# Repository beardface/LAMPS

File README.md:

LAMPS - The Open Hardware SLA Printer
-------------------------------------
LAMPS (Laser Arduino Mega Pololu Shield|SLA Printer) is an open control board and SLA printer design.  The SLA Printer strives to be a low-cost, small footprint (It is only 200mmx350mm!), highly capable SLA Printer. The build platform size is currently 100mmx100mm, but could probably be increased by someone who is motivated to enhance the design.

#License
The schematic for the OpenSL electronics are licensed under the GPL.

The printer and its associated parts are licensed under the Creative Commons Attribution-NonCommercial-ShareAlike 3.0 Unported License.

Basically, use my design all you want! :) But, don't sell it.  If you want an exception, contact me.

#LAMPS Board
LAMPS is the PCB control board that rides on top of an Arduino Mega 2560.  It provides Galvanometer control (Through 12 bit DACs).  It also controls the laser, buttons, Z Stepper Motor (Through Pololu Carrier), End Stops, LEDs, etc...  (It is the Brainz).

Version 1.0 of the LAMPS board has been manufactured and tested... I found a few issues with the board and am currently redesigning and removing a few unnecessary components for 1.1. Release date T.B.D.

#Firmware
The firmware for LAMPS is a fork of Marlin (The best open source RepRap firmware I know of), and can be found here: https://github.com/beardface/Marlin-OpenSL
The firmware is very much an active work-in-progress, and I encourage you to fork, and contribute.

#LAMPS Printer Parts -WARNING... THIS IS NOT UP TO DATE-
All of the parts are available as sketchup (skp) and stl files.

##Printed Parts
* 1x [Laser Mount](https://github.com/beardface/LAMPS/blob/master/parts/lasermount.stl)
* 1x [Mirror Mount](https://github.com/beardface/LAMPS/blob/master/parts/mirrormount.stl)
* 4x [Vibrating Vat Mount](https://github.com/beardface/LAMPS/blob/master/parts/vibrating_vat_mount.stl)
* 1x [Z-Axis Top Mount](https://github.com/beardface/LAMPS/blob/master/parts/z_top_mount.stl)
* 1x [Z-Axis Bottom Mount](https://github.com/beardface/LAMPS/blob/master/parts/z_bottom_mount.stl)
* 1x [Build Platform Mount](https://github.com/beardface/LAMPS/blob/master/parts/platform_mount.stl)
* 1x [Build Stage](https://github.com/beardface/LAMPS/blob/master/parts/build_platform_connector.stl)
* 1x Endstop Mount

##Laser Cut Parts
###Platform
Use 3/16"-1/4" thick acrylic for the platforms.
* 1x [Vat Platform](https://github.com/beardface/LAMPS/blob/master/parts/top_platform.svg)
* 1x [Component Platform](https://github.com/beardface/LAMPS/blob/master/parts/bottom_platform.svg)
* 1x 80mmx80mm 1/4"Acryilc Stage Mount (leftover part from cutting of top_platform)

###VAT
Use 1/4" Clear (Transparent) Acrylic for the VAT!
* 1x [Vat Back](https://github.com/beardface/LAMPS/blob/master/parts/vat_design/vat_back.svg)
* 1x [Vat Front](https://github.com/beardface/LAMPS/blob/master/parts/vat_design/vat_front.svg)
* 1x [Vat Bottom](https://github.com/beardface/LAMPS/blob/master/parts/vat_design/vat_bottom.svg)
* 1x [Vat Handle](https://github.com/beardface/LAMPS/blob/master/parts/vat_design/vat_handle.svg)
* 2x [Vat Sides](https://github.com/beardface/LAMPS/blob/master/parts/vat_design/vat_side.svg)

##Non-Printed Parts
* 1x NEMA 17 Stepper Motor (Low Profile!)
* 2x 8mm Smooth Rod (~260mm)
* 1x 8mm Threaded Rod (~260mm) and 2-M8 nuts
* 4x LM8UU Bearings
* 1x LAMPS Electronics Kit (w/Pololu and 2x endstops)
* 1x LAMPS PCB Build Platform
* 1x LAMPS Musimi 2020 Rail Kit and connectors
  * 4x  350mm 2020 Extrusions w/end tapping holes
  * 11x 160mm 2020 Extrusions
  * 1x  110mm 2020 Extrusion
* 1x LAMPS Enclsoure & Hatch Kit
* 1x 405nm Laser (20mw-150mw) -- Build properties/cure time/etc... vary by laser!
* 1x 3" Square Mirror
* 1x Laser Galvo Set (20kpps) w/power supply
 * Resistance Configuration (Note to Self)
  * AXIS  |  SIZE     | GAIN      | LF         | HF        | LINEAR
  * X     |  4.96Kohm | 4.68 Kohm | 26.36 Kohm | 4.78 Kohm | 1.75 Kohm
  * Y     |  6.1Kohm  | 4.18 Kohm | 26.47 Kohm | 4.37 Kohm | 2.3 Kohm
* 1x +/-12V Power Supply (~1-3Amps)
* USB Cable
* Power Cable
* Screws, Nuts, Wires, Solder, Patience

##Optional (But Useful) Non-Printed Parts
* 1xLCD Screen
* 1xSD Card Reader (and corresponding circuit... T.B.D.)
* 1x Power Switch (110-250VAC), lighted
* 1x Power Terminal (Two combine power into single input)
* 1x 3-Prong Power Jack
 
###LAMPS IS A WORK IN PROGRESS.

##Some words of Caution
* Careful with 110-250VAC, it can --bite-- Seriously Harm you if you aren't careful
* Some 405nm Resins can be toxic while curing- take the appropriate measures to ensure you are working in a well ventelated room

~LAMPS design, details, and parts list are provided without any warranty or gaurantee- this is a community project, so lets work together to solve issues that may arise!

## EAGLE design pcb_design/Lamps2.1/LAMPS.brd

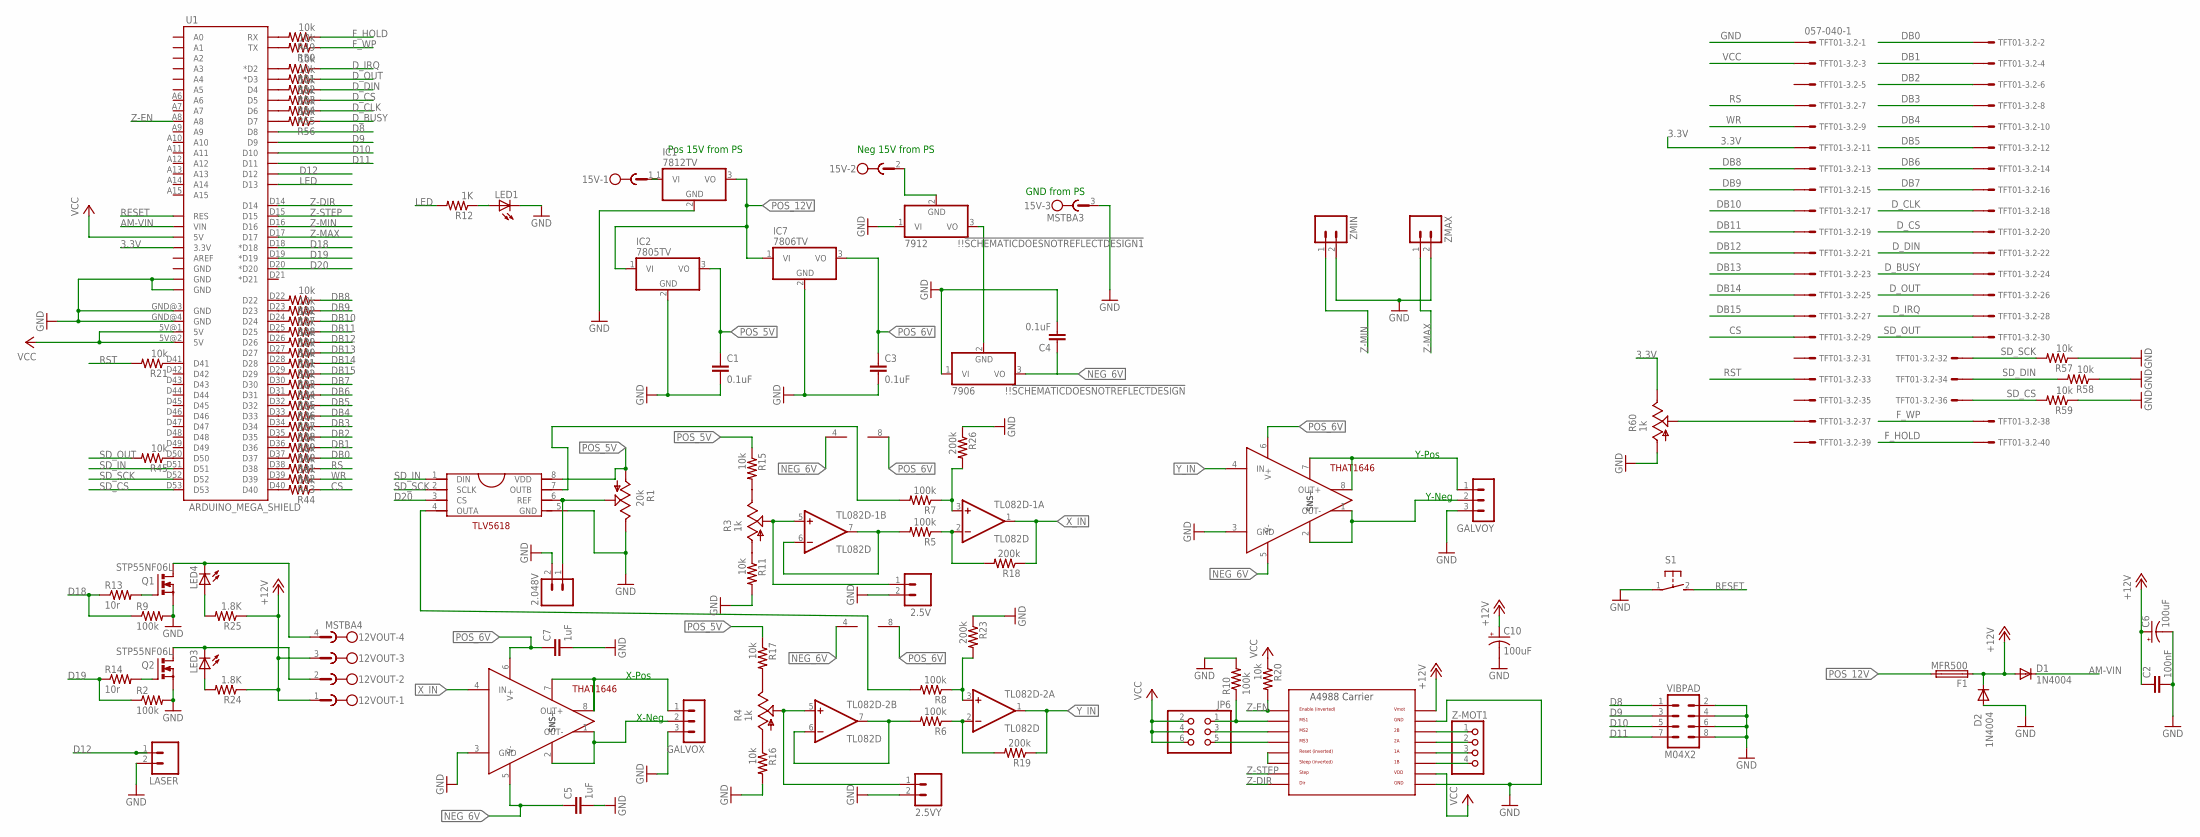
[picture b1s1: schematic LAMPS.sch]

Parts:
2.5V, 2.5VY, 2.048V: M02PTH; 1X02
12VOUT: MSTBA4
15V: MSTBA3; MPN 1757255
!!!SCHEMATICDOESNOTREFLECTDESIGN: 7906; TO220V; MPN KA7906TU
!!!SCHEMATICDOESNOTREFLECTDESIGN1: 7912; TO220V; MPN KA7906TU
C1, C3, C4: 0.1uF; C2.5-2
C2: 100nF; C0805
C5, C7: 1uF; C2.5-2
C6, C10: 100uF; 153CLV-0605
D1, D2: 1N4004; DO41-10
F1: MFR500
GALVOX: 3PIN-HEADER
GALVOY: 3PIN-HEADER
IC1: 7812TV; TO220V
IC2: 7805TV; TO220V
IC7: 7806TV; TO220V
JP6: PINHD-2X3; 2X03
LASER: M02PTH; 1X02
LED1, LED3, LED4: LEDCHIP-LED0805; CHIP-LED0805
Q1, Q2: STP55NF06L; TO220BV; MPN IRF1010EZPBF
R1: 20k; B25P
R2, R5, R6, R7, R8, R9, R10: 100k; R0805
R3, R4, R60: 1k; B25P
R11, R15, R16, R17, R20, R21, R22, R27, R28, R29, R30, R31, R32, R33, R34, R35, R36, R37, R38, R39, R40, R41, R42, R43, R44, R45, R49, R50, R51, R52, R53, R54, R55, R56, R57, R58, R59: 10k; R0805
R12: 1K; R0805
R13: 10r; R0805
R14: 10r; M0805
R18, R19, R23, R26: 200k; R0805
R24, R25: 1.8K; R0805
S1: 31-XX; B3F-31XX
TFT01-3.2: 057-040-1
TL082D-1, TL082D-2: TL082D; SO08
U1: ARDUINO_MEGA_SHIELD
U$1, U$4: THAT1646; MPN THAT1646P08-U
U$2: THAT1646SMD; TLV5618
U$8: A4988BREAKOUT
VIBPAD: M04X2; 2X4
Z-MOT1: PINHD-1X4; 1X04
ZMAX: M02PTH; 1X02
ZMIN: M02PTH; 1X02

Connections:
3.3V: R60.E, TFT01-3.2.11, U1.3.3V
+12V: 12VOUT.1, 12VOUT.3, C2.1, C6.+, C10.+, D1.A, D2.C, F1.1, R24.1, R25.1, U$8.VMOT
AM-VIN: D1.C, U1.VIN
CS: R44.1, TFT01-3.2.29
D8: U1.D8, VIBPAD.1
D9: U1.D9, VIBPAD.3
D10: U1.D10, VIBPAD.5
D11: U1.D11, VIBPAD.7
D12: LASER.1, U1.D12
D18: R9.1, R13.1, U1.D18 (*D18)
D19: R2.1, R14.1, U1.D19 (*D19)
D20: U1.D20 (*D20), U$2.3 (CS)
DB0: R41.1, TFT01-3.2.2
DB1: R40.1, TFT01-3.2.4
DB2: R39.1, TFT01-3.2.6
DB3: R38.1, TFT01-3.2.8
DB4: R37.1, TFT01-3.2.10
DB5: R36.1, TFT01-3.2.12
DB6: R35.1, TFT01-3.2.14
DB7: R34.1, TFT01-3.2.16
DB8: R22.1, TFT01-3.2.13
DB9: R27.1, TFT01-3.2.15
DB10: R28.1, TFT01-3.2.17
DB11: R29.1, TFT01-3.2.19
DB12: R30.1, TFT01-3.2.21
DB13: R31.1, TFT01-3.2.23
DB14: R32.1, TFT01-3.2.25
DB15: R33.1, TFT01-3.2.27
D_BUSY: R56.1, TFT01-3.2.24
D_CLK: R55.1, TFT01-3.2.18
D_CS: R54.1, TFT01-3.2.20
D_DIN: R53.1, TFT01-3.2.22
D_IRQ: R51.1, TFT01-3.2.28
D_OUT: R52.1, TFT01-3.2.26
F_HOLD: R49.1, TFT01-3.2.40
F_WP: R50.1, TFT01-3.2.38
GND: 2.5V.2, 2.5VY.2, 2.048V.2, 15V.3, !!!SCHEMATICDOESNOTREFLECTDESIGN.1 (VI), !!!SCHEMATICDOESNOTREFLECTDESIGN1.1 (VI), C1.2, C2.2, C3.2, C4.2, C5.2, C6.-, C7.2, C10.-, GALVOX.3, GALVOY.3, IC1.2 (GND), IC2.2 (GND), IC7.2 (GND), LASER.2, LED1.C, Q1.S, Q2.S, R1.E, R2.2, R9.2, R10.2, R11.2, R16.2, R23.1, R26.1, R57.1, R58.1, R59.1, R60.A, S1.1, TFT01-3.2.1, U1.GND@0 (GND), U1.GND@1 (GND), U1.GND@3 (GND), U1.GND@4 (GND), U$1.3 (GND), U$2.5 (GND), U$4.3 (GND), U$8.GND, U$8.GND@0 (GND), VIBPAD.2, VIBPAD.4, VIBPAD.6, VIBPAD.8, ZMAX.2, ZMIN.2
GND_0: D2.A
LED: R12.2, U1.D13
unnamed: 12VOUT.2, LED3.C, Q2.D
unnamed: R21.1, U1.D41
unnamed: !!!SCHEMATICDOESNOTREFLECTDESIGN.2 (GND), !!!SCHEMATICDOESNOTREFLECTDESIGN1.3 (VO)
unnamed: R4.A, R16.1
unnamed: R4.E, R17.2
unnamed: 2.048V.1, R1.S, U$2.6 (REF)
unnamed: 12VOUT.4, LED4.C, Q1.D
unnamed: R3.A, R11.1
unnamed: R3.E, R15.2
unnamed: 2.5VY.1, R4.S, TL082D-2.5 (+IN)
unnamed: 2.5V.1, R3.S, TL082D-1.5 (+IN)
unnamed: GALVOX.2, U$1.1 (OUT-), U$1.2 (SNS-)
unnamed: GALVOX.1, U$1.7 (SNS+), U$1.8 (OUT+)
unnamed: R5.2, TL082D-1.6 (-IN), TL082D-1.7 (OUT)
unnamed: R5.1, R18.2, TL082D-1.2 (-IN)
unnamed: R7.2, U$2.7 (OUTB)
unnamed: R7.1, R26.2, TL082D-1.3 (+IN)
unnamed: R6.2, TL082D-2.6 (-IN), TL082D-2.7 (OUT)
unnamed: R22.2, U1.D22
unnamed: R6.1, R19.2, TL082D-2.2 (-IN)
unnamed: R8.2, U$2.4 (OUTA)
unnamed: R8.1, R23.2, TL082D-2.3 (+IN)
unnamed: R27.2, U1.D23
unnamed: GALVOY.2, U$4.1 (OUT-), U$4.2 (SNS-)
unnamed: GALVOY.1, U$4.7 (SNS+), U$4.8 (OUT+)
unnamed: R28.2, U1.D24
unnamed: R29.2, U1.D25
unnamed: R30.2, U1.D26
unnamed: R31.2, U1.D27
unnamed: R32.2, U1.D28
unnamed: R33.2, U1.D29
unnamed: R34.2, U1.D30
unnamed: R35.2, U1.D31
unnamed: R36.2, U1.D32
unnamed: R37.2, U1.D33
unnamed: R38.2, U1.D34
unnamed: JP6.3, U$8.MS2
unnamed: U$8.RST, U$8.SLP (SLEEP)
unnamed: JP6.5, U$8.MS3
unnamed: JP6.1, R10.1, U$8.MS1
unnamed: U$8.2B, Z-MOT1.1
unnamed: U$8.2A, Z-MOT1.2
unnamed: U$8.1A, Z-MOT1.3
unnamed: U$8.1B, Z-MOT1.4
unnamed: LED3.A, R24.2
unnamed: LED1.A, R12.1
unnamed: Q2.G, R14.2
unnamed: Q1.G, R13.2
unnamed: R39.2, U1.D35
unnamed: LED4.A, R25.2
unnamed: R40.2, U1.D36
unnamed: R41.2, U1.D37
unnamed: R42.2, U1.D38
unnamed: R43.2, U1.D39
unnamed: R44.2, U1.D40
unnamed: R45.1, U1.D50
unnamed: 15V.1, IC1.1 (VI)
unnamed: 15V.2, !!!SCHEMATICDOESNOTREFLECTDESIGN1.2 (GND)
unnamed: R49.2, U1.RX
unnamed: R50.2, U1.TX
unnamed: R51.2, U1.D2 (*D2)
unnamed: R52.2, U1.D3 (*D3)
unnamed: R53.2, U1.D4
unnamed: R54.2, U1.D5
unnamed: R55.2, U1.D6
unnamed: R56.2, U1.D7
unnamed: R60.S, TFT01-3.2.37
NEG_6V: !!!SCHEMATICDOESNOTREFLECTDESIGN.3 (VO), C4.1, C5.1, TL082D-1.4 (V-), TL082D-2.4 (V-), U$1.5 (V-)
POS_5V: C1.1, IC2.3 (VO), R1.A, R15.1, R17.1, U$2.8 (VDD)
POS_6V: C3.1, C7.1, IC7.3 (VO), TL082D-1.8 (V+), TL082D-2.8 (V+), U$1.6 (V+), U$4.6 (V+)
POS_12V: F1.2, IC1.3 (VO), IC2.1 (VI), IC7.1 (VI)
RESET: S1.2 (S), U1.RES
RS: R42.1, TFT01-3.2.7
RST: R21.2, TFT01-3.2.33
SD_CS: R59.2, TFT01-3.2.36, U1.D53
SD_DIN: R58.2, TFT01-3.2.34
SD_IN: U1.D51, U$2.1 (DIN)
SD_OUT: R45.2, TFT01-3.2.30
SD_SCK: R57.2, TFT01-3.2.32, U1.D52, U$2.2 (SCLK)
T2_5: U$4.5 (V-)
VCC: JP6.2, JP6.4, JP6.6, R20.1, TFT01-3.2.3, U1.5V@0 (5V), U1.5V@1 (5V), U1.5V@2 (5V), U$8.VDD
WR: R43.1, TFT01-3.2.9
X_IN: R18.1, TL082D-1.1 (OUT), U$1.4 (IN)
Y_IN: R19.1, TL082D-2.1 (OUT), U$4.4 (IN)
Z-DIR: U1.D14, U$8.DIR
Z-EN: R20.2, U1.A8, U$8.EN
Z-MAX: U1.D17, ZMAX.1
Z-MIN: U1.D16, ZMIN.1
Z-STEP: U1.D15, U$8.STEP

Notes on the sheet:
X-Pos
X-Neg
Y-Pos
Y-Neg
Pos 15V from PS
Neg 15V from PS
GND from PS

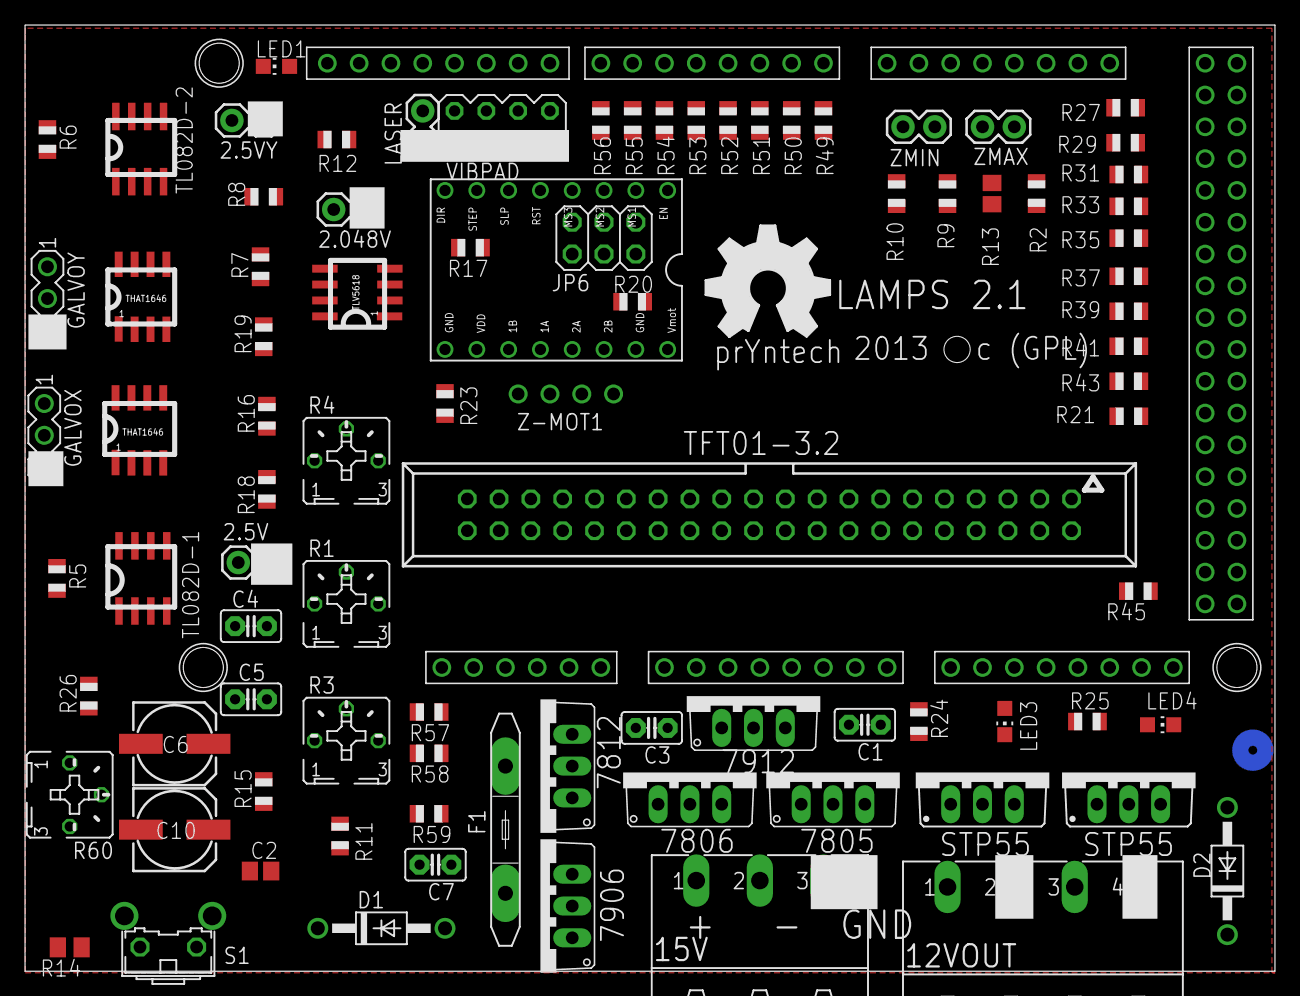
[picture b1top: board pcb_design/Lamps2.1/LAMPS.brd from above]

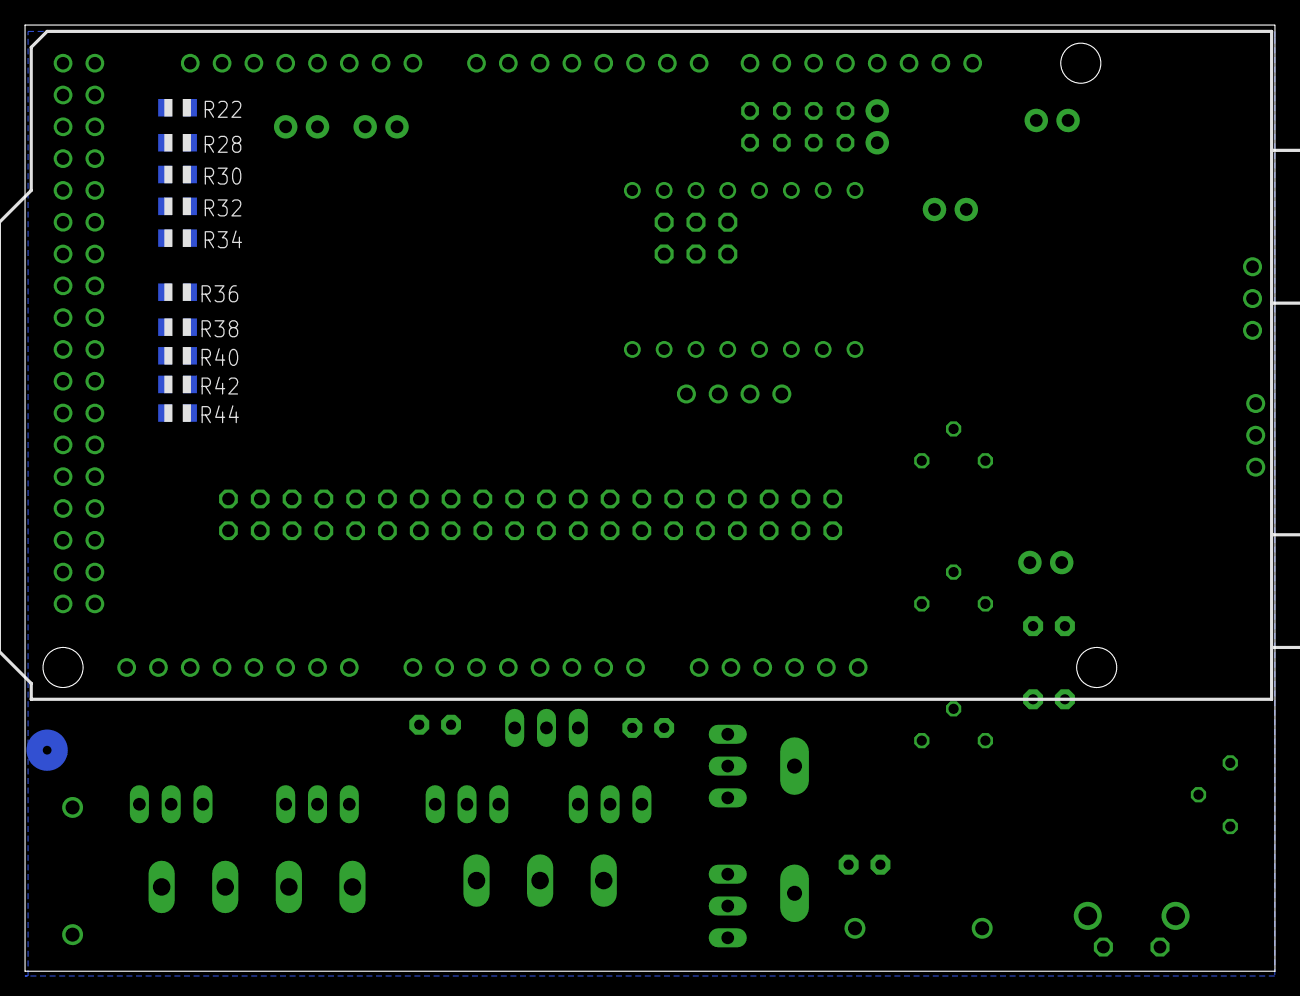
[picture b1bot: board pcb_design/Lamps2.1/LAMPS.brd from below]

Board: 2 copper layers, 99.8 x 75.6 mm, 101 parts (10 on the bottom side), 126 nets.

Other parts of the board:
U$3: OSHW_FILLX350_NOTEXT

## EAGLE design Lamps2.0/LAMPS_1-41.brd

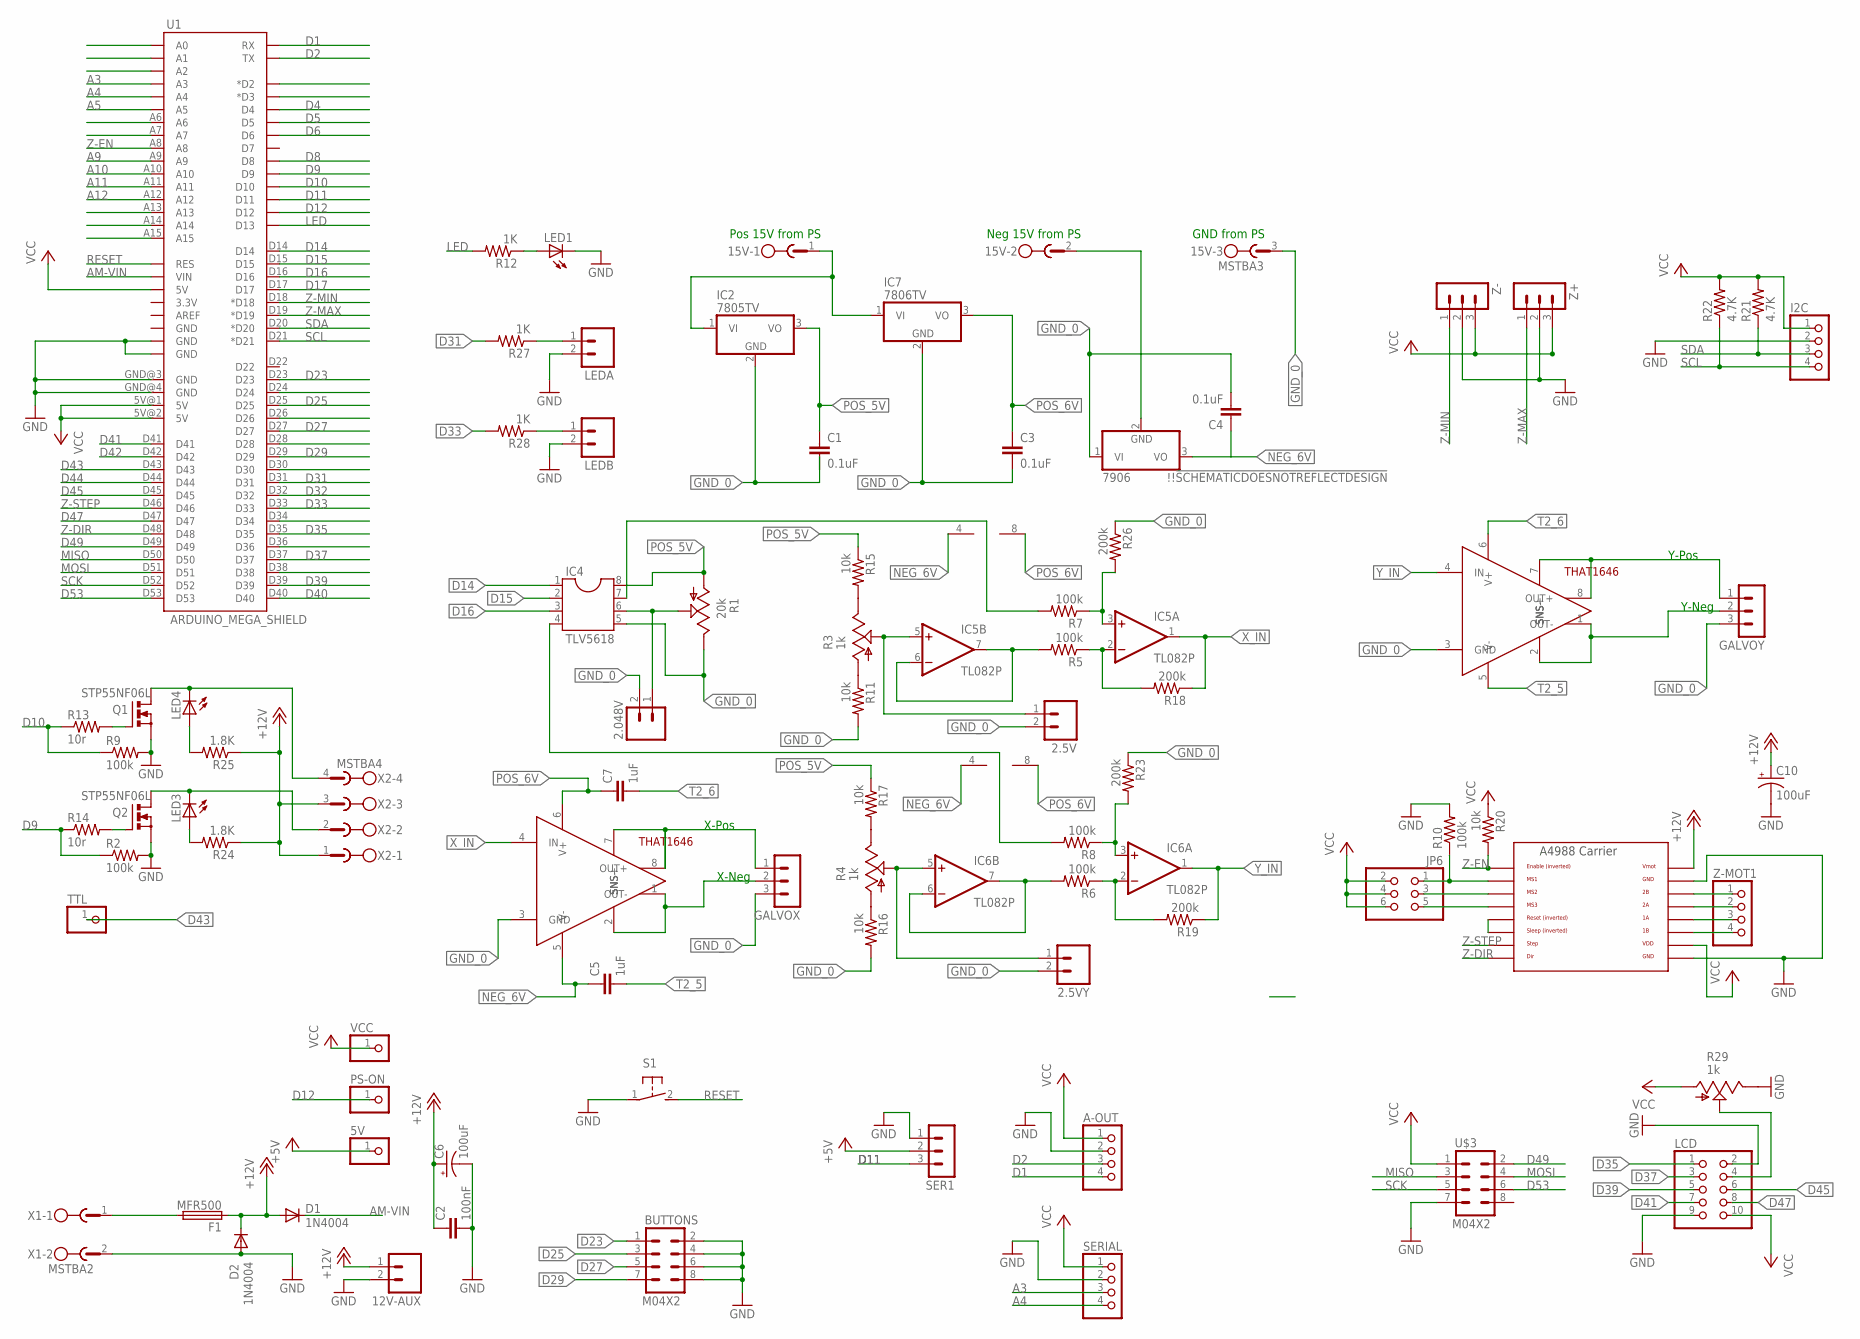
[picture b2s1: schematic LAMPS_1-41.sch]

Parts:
2.5V, 2.5VY, 2.048V, 12V-AUX: M02PTH; 1X02
5V: PINHD-1X1; 1X01
15V: MSTBA3
!!!SCHEMATICDOESNOTREFLECTDESIGN: 7906; TO220V
A-OUT: PINHD-1X4; 1X04
BUTTONS: M04X2; 2X4
C1, C3, C4: 0.1uF; C2.5-2
C2: 100nF; C0805
C5, C7: 1uF; C2.5-2
C6, C10: 100uF; 153CLV-0605
D1, D2: 1N4004; DO41-10
F1: MFR500
GALVOX: 3PIN-HEADER
GALVOY: 3PIN-HEADER
I2C: PINHD-1X4; 1X04
IC2: 7805TV; TO220V
IC4: TLV5618; SOCKET-08
IC5, IC6: TL082P; DIL08
IC7: 7806TV; TO220V
JP6: PINHD-2X3; 2X03
LCD: PINHD-2X5; 2X05
LED1, LED3, LED4: LEDCHIP-LED0805; CHIP-LED0805
LEDA: M02PTH; 1X02
LEDB: M02PTH; 1X02
PS-ON: PINHD-1X1; 1X01
Q1, Q2: STP55NF06L; TO220BV
R1: 20k; B25P
R2, R5, R6, R7, R8, R9, R10: 100k; R0805
R3, R4, R29: 1k; B25P
R11, R15, R16, R17, R20: 10k; R0805
R12, R27, R28: 1K; R0805
R13: 10r; R0805
R14: 10r; M0805
R18, R19, R23, R26: 200k; R0805
R21, R22: 4.7K; R0805
R24, R25: 1.8K; R0805
S1: 31-XX; B3F-31XX
SER1: 3PIN-HEADER
SERIAL: PINHD-1X4; 1X04
TTL: PINHD-1X1; 1X01
U1: ARDUINO_MEGA_SHIELD
U$1, U$4: THAT1646
U$3: M04X2; 2X4
U$8: A4988BREAKOUT
VCC: PINHD-1X1; 1X01
X1: MSTBA2
X2: MSTBA4
Z+: 3PIN-HEADER
Z-: 3PIN-HEADER
Z-MOT1: PINHD-1X4; 1X04

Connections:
+5V: 5V.1, SER1.2
+12V: 12V-AUX.1, C2.1, C6.+, C10.+, D1.A, D2.C, F1.1, R24.1, R25.1, U$8.VMOT, X2.1, X2.3; also elsewhere on the board
A3: SERIAL.3, U1.A3
A4: SERIAL.4, U1.A4
A5: U1.A5
A9: U1.A9
A10: U1.A10
A11: U1.A11
A12: U1.A12
AM-VIN: D1.C, U1.VIN
D1: A-OUT.4, U1.RX
D2: A-OUT.3, U1.TX
D4: U1.D4
D5: U1.D5
D6: U1.D6
D8: U1.D8
D9: R2.1, R14.1, U1.D9
D10: R9.1, R13.1, U1.D10
D11: SER1.3, U1.D11
D12: PS-ON.1, U1.D12
D14: IC4.1, U1.D14
D15: IC4.2, U1.D15
D16: IC4.3, U1.D16
D17: U1.D17
D31: R27.2, U1.D31
D33: R28.2, U1.D33
D35: LCD.1, U1.D35
D37: LCD.3, U1.D37
D39: LCD.5, U1.D39
D40: U1.D40
D41: LCD.7, U1.D41
D42: U1.D42
D43: TTL.1, U1.D43
D44: U1.D44
D45: LCD.6, U1.D45
D47: LCD.8, U1.D47
D49: U1.D49, U$3.2
D53: U1.D53, U$3.6
E0-DIR: U1.D28
E0-EN: U1.D24
E0-STEP: U1.D26
E1-EN: U1.D30
GND: 12V-AUX.2, A-OUT.2, BUTTONS.2, BUTTONS.4, BUTTONS.6, BUTTONS.8, C2.2, C6.-, C10.-, D2.A, I2C.2, LCD.2, LCD.9, LED1.C, LEDA.2, LEDB.2, Q1.S, Q2.S, R2.2, R9.2, R10.2, R29.E, S1.1, SER1.1, SERIAL.2, U1.GND@0 (GND), U1.GND@1 (GND), U1.GND@3 (GND), U1.GND@4 (GND), U$3.7, U$8.GND, U$8.GND@0 (GND), X1.2, Z+.2, Z-.2; also elsewhere on the board
GND_0: 2.5V.2, 2.5VY.2, 2.048V.2, 15V.3, !!!SCHEMATICDOESNOTREFLECTDESIGN.1 (VI), C1.2, C3.2, C4.2, GALVOX.3, GALVOY.3, IC2.2 (GND), IC4.5, IC7.2 (GND), R1.E, R11.2, R16.2, R23.1, R26.1, U$1.3 (GND), U$4.3 (GND)
LED: R12.2, U1.D13
MISO: U1.D50, U$3.3
MOSI: U1.D51, U$3.4
unnamed 47: LED3.C, Q2.D, X2.2; also elsewhere on the board
unnamed: 15V.1, IC2.1 (VI), IC7.1 (VI)
unnamed: 15V.2, !!!SCHEMATICDOESNOTREFLECTDESIGN.2 (GND)
unnamed: R4.A, R16.1
unnamed: R4.E, R17.2
unnamed: 2.048V.1, IC4.6, R1.S
unnamed 53: LED4.C, Q1.D, X2.4; also elsewhere on the board
unnamed: R3.A, R11.1
unnamed: R3.E, R15.2
unnamed: 2.5VY.1, IC6.5 (+IN), R4.S
unnamed: 2.5V.1, IC5.5 (+IN), R3.S
unnamed: GALVOX.2, U$1.1 (OUT-), U$1.2 (SNS-)
unnamed: GALVOX.1, U$1.7 (SNS+), U$1.8 (OUT+)
unnamed: IC5.6 (-IN), IC5.7 (OUT), R5.2
unnamed: IC5.2 (-IN), R5.1, R18.2
unnamed: IC4.7, R7.2
unnamed: IC5.3 (+IN), R7.1, R26.2
unnamed: IC6.6 (-IN), IC6.7 (OUT), R6.2
unnamed: LEDA.1, R27.1
unnamed: IC6.2 (-IN), R6.1, R19.2
unnamed: IC4.4, R8.2
unnamed: IC6.3 (+IN), R8.1, R23.2
unnamed: LEDB.1, R28.1
unnamed: GALVOY.2, U$4.1 (OUT-), U$4.2 (SNS-)
unnamed: GALVOY.1, U$4.7 (SNS+), U$4.8 (OUT+)
unnamed: LCD.4, R29.S
unnamed: JP6.3, U$8.MS2
unnamed: U$8.RST, U$8.SLP (SLEEP)
unnamed: JP6.5, U$8.MS3
unnamed: JP6.1, R10.1, U$8.MS1
unnamed: U$8.2B, Z-MOT1.1
unnamed: U$8.2A, Z-MOT1.2
unnamed: U$8.1A, Z-MOT1.3
unnamed: U$8.1B, Z-MOT1.4
unnamed: LED3.A, R24.2
unnamed: LED1.A, R12.1
unnamed: Q2.G, R14.2
unnamed: Q1.G, R13.2
unnamed: LED4.A, R25.2
unnamed 86: F1.2, X1.1; also elsewhere on the board
NEG_6V: !!!SCHEMATICDOESNOTREFLECTDESIGN.3 (VO), C4.1, C5.1, IC5.4 (V-), IC6.4 (V-), U$1.5 (V-)
POS_5V: C1.1, IC2.3 (VO), IC4.8, R1.A, R15.1, R17.1
POS_6V: C3.1, C7.1, IC5.8 (V+), IC6.8 (V+), IC7.3 (VO), U$1.6 (V+)
RESET: S1.2 (S), U1.RES
SCK: U1.D52, U$3.5
SCL: I2C.4, R22.1, U1.D21 (*D21)
SDA: I2C.3, R21.1, U1.D20 (*D20)
T2_5: C5.2, U$4.5 (V-)
T2_6: C7.2, U$4.6 (V+)
THERM0: U1.A13
THERM1: U1.A14
THERM2: U1.A15
VCC: A-OUT.1, I2C.1, JP6.2, JP6.4, JP6.6, LCD.10, R20.1, R21.2, R22.2, R29.A, SERIAL.1, U1.5V@0 (5V), U1.5V@1 (5V), U1.5V@2 (5V), U$3.1, U$8.VDD, VCC.1, Z+.3, Z-.3
X-DIR: U1.A1
X-MAX: U1.D2 (*D2)
X-MIN: U1.D3 (*D3)
X-STEP: U1.A0
X_IN: IC5.1 (OUT), R18.1, U$1.4 (IN)
Y-DIR: U1.A7
Y-EN: U1.A2
Y-STEP: U1.A6
Y_IN: IC6.1 (OUT), R19.1, U$4.4 (IN)
Z-DIR: U1.D48, U$8.DIR
Z-EN: R20.2, U1.A8, U$8.EN
Z-MAX: U1.D19 (*D19), Z+.1
Z-MIN: U1.D18 (*D18), Z-.1
Z-STEP: U1.D46, U$8.STEP

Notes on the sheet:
X-Pos
X-Neg
Y-Pos
Y-Neg
Pos 15V from PS
Neg 15V from PS
GND from PS

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
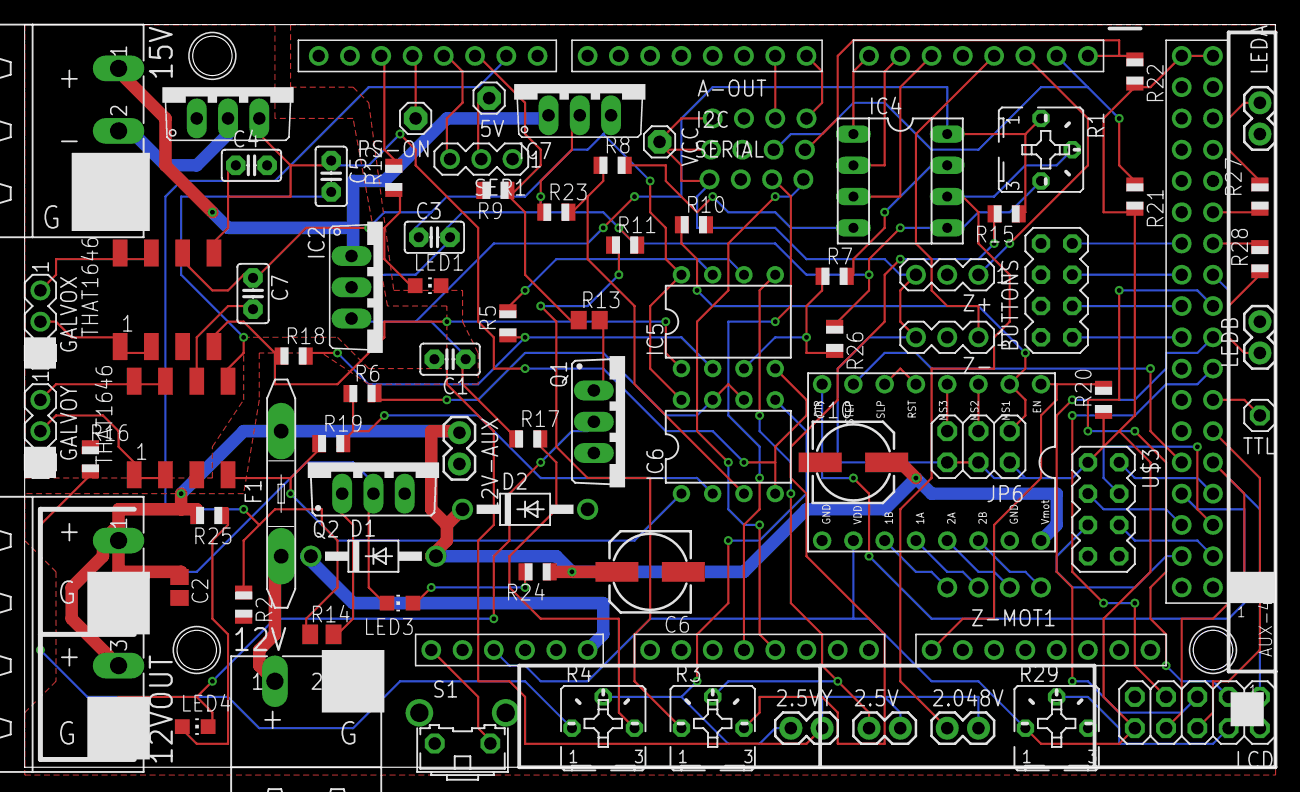
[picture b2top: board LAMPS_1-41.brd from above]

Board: 2 copper layers, 101.6 x 60.3 mm, 83 parts (1 on the bottom side), 91 nets.

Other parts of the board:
12V: MSTBA2
12VOUT: MSTBA4
U$2: OSHW_FILLX1000_NOTEXT

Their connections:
+12V: 12VOUT.1, 12VOUT.3; also elsewhere on the board
GND: 12V.2; also elsewhere on the board
unnamed 47: 12VOUT.2; also elsewhere on the board
unnamed 53: 12VOUT.4; also elsewhere on the board
unnamed 86: 12V.1; also elsewhere on the board

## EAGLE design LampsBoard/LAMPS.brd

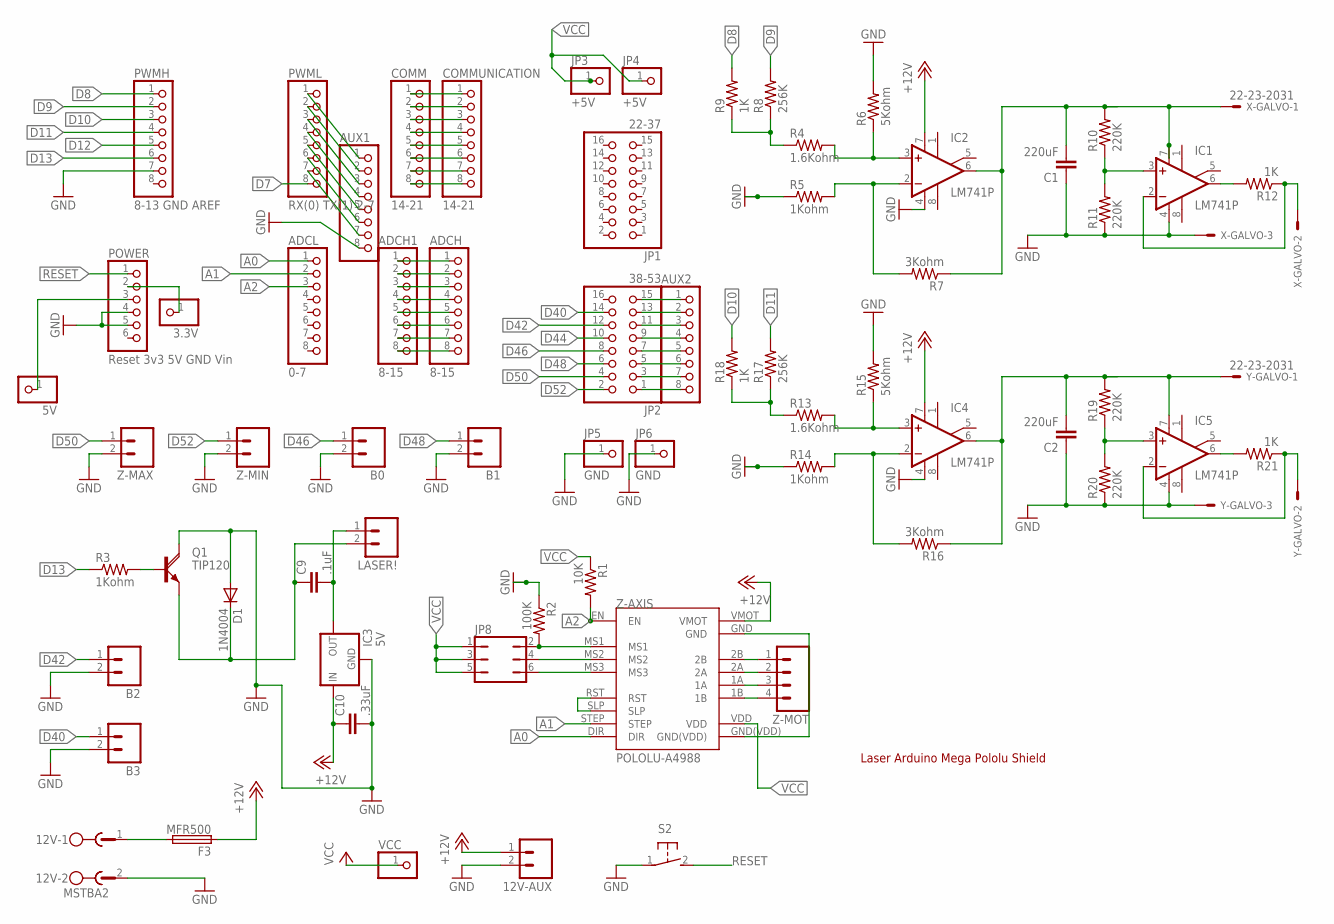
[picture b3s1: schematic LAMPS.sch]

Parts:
3.3V, 5V: PINHD-1X1; 1X01
12V: MSTBA2; MPN 1757242
12V-AUX: M02PTH; 1X02
ADCH, ADCH1: 8-15; 1X08
ADCL: 0-7; 1X08
AUX1, AUX2: 14-21; 1X08
B0, B1, B2, B3: M02PTH; 1X02
C1, C2: 220uF; CAP-PTH-SMALL; MPN 100PK220MEFC12.5X20
C9: .1uF; CAP-PTH-SMALL
C10: .33uF; CAP-PTH-SMALL
COMM: 14-21; 1X08
COMMUNICATION: 14-21; 1X08
D1: 1N4004; DO41-10
F3: MFR500
IC1, IC2, IC4, IC5: LM741P; DIL08
IC3: 5V; 78XXL
JP1: 22-37; 2X08
JP2: 38-53; 2X08
JP3, JP4: +5V; 1X01
JP5, JP6: GND; 1X01
JP8: JP3Q
LASER!: M02POLAR; MOLEX-1X2
POWER: Reset 3v3 5V GND Vin; 1X06
PWMH: 8-13 GND AREF; 1X08
PWML: RX(0) TX(1) 2-7; 1X08
Q1: TIP120; TO220AH
R1: 10K; AXIAL-0.3
R2: 100K; AXIAL-0.3
R3, R5, R14: 1Kohm; AXIAL-0.3
R4, R13: 1.6Kohm; AXIAL-0.3
R6, R15: 5Kohm; AXIAL-0.3
R7, R16: 3Kohm; AXIAL-0.3
R8, R17: 256K; AXIAL-0.3
R9, R12, R18, R21: 1K; AXIAL-0.3
R10, R11, R19, R20: 220K; AXIAL-0.3
S2: 31-XX; B3F-31XX; MPN B3F-3100
VCC: PINHD-1X1; 1X01
X-GALVO: 22-23-2031; MPN 22-23-2031
Y-GALVO: 22-23-2031; MPN 22-23-2031
Z-AXIS: POLOLU-A4988; DIL_A4988
Z-MAX: M02PTH; 1X02
Z-MIN: M02PTH; 1X02
Z-MOT: M04POLAR; MOLEX-1X4

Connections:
+12V: 12V-AUX.1, C10.1, F3.1, IC2.7 (V+), IC3.IN, IC4.7 (V+), Z-AXIS.VMOT
A0: ADCL.1, Z-AXIS.DIR
A1: ADCL.2, Z-AXIS.STEP
A2: ADCL.3, R1.P$2 (2), Z-AXIS.EN
D7: PWML.8
D8: PWMH.1, R9.P$2 (2)
D9: PWMH.2, R8.P$2 (2)
D10: PWMH.3, R18.P$2 (2)
D11: PWMH.4, R17.P$2 (2)
D12: PWMH.5
D13: PWMH.6, R3.P$1 (1)
D40: B3.1, JP2.14
D42: B2.1, JP2.12
D44: JP2.10, Q1.B, R3.P$2 (2)
D46: B0.1, JP2.8
D48: B1.1, JP2.6
D50: JP2.4, Z-MAX.1
D52: JP2.2, Z-MIN.1
GND: 12V.2, 12V-AUX.2, AUX1.8, B0.2, B1.2, B2.2, B3.2, C1.1, C2.1, C10.2, D1.A, IC1.4 (V-), IC2.4 (V-), IC3.GND, IC4.4 (V-), IC5.4 (V-), JP5.1, JP6.1, POWER.4, POWER.5, PWMH.7, Q1.C, R2.P$1 (1), R5.P$1 (1), R6.P$2 (2), R11.P$1 (1), R14.P$1 (1), R15.P$2 (2), R20.P$1 (1), S2.1, X-GALVO.3, Y-GALVO.3, Z-MAX.2, Z-MIN.2
unnamed: IC2.3 (+IN), R4.P$2 (2), R6.P$1 (1)
unnamed: IC2.2 (-IN), R5.P$2 (2), R7.P$2 (2)
unnamed: IC1.3 (+IN), R10.P$1 (1), R11.P$2 (2)
unnamed: R4.P$1 (1), R8.P$1 (1), R9.P$1 (1)
unnamed: IC4.3 (+IN), R13.P$2 (2), R15.P$1 (1)
unnamed: C1.2, IC1.7 (V+), IC2.6 (OUT), R7.P$1 (1), R10.P$2 (2), X-GALVO.1
unnamed: IC1.6 (OUT), R12.P$2 (2)
unnamed: 3.3V.1, POWER.2
unnamed: COMM.1, COMMUNICATION.1
unnamed: 5V.1, POWER.3
unnamed: Z-AXIS.RST, Z-AXIS.SLP
unnamed: C9.2, IC3.OUT, LASER!.1
unnamed: C9.1, D1.C, LASER!.2, Q1.E
unnamed: Z-AXIS.GND, Z-AXIS.GND(VDD)
unnamed: JP8.2, R2.P$2 (2), Z-AXIS.MS1
unnamed: JP8.4, Z-AXIS.MS2
unnamed: JP8.6, Z-AXIS.MS3
unnamed: IC1.2 (-IN), R12.P$1 (1), X-GALVO.2
unnamed: IC4.2 (-IN), R14.P$2 (2), R16.P$2 (2)
unnamed: Z-AXIS.2B, Z-MOT.1
unnamed: Z-AXIS.2A, Z-MOT.2
unnamed: Z-AXIS.1A, Z-MOT.3
unnamed: Z-AXIS.1B, Z-MOT.4
unnamed: R13.P$1 (1), R17.P$1 (1), R18.P$1 (1)
unnamed: C2.2, IC4.6 (OUT), IC5.7 (V+), R16.P$1 (1), R19.P$2 (2), Y-GALVO.1
unnamed: IC5.3 (+IN), R19.P$1 (1), R20.P$2 (2)
unnamed: IC5.6 (OUT), R21.P$2 (2)
unnamed: IC5.2 (-IN), R21.P$1 (1), Y-GALVO.2
unnamed: COMM.2, COMMUNICATION.2
unnamed: COMM.3, COMMUNICATION.3
unnamed: 12V.1, F3.2
unnamed: COMM.4, COMMUNICATION.4
unnamed: COMM.5, COMMUNICATION.5
unnamed: COMM.6, COMMUNICATION.6
unnamed: COMM.7, COMMUNICATION.7
unnamed: COMM.8, COMMUNICATION.8
unnamed: ADCH.1, ADCH1.1
unnamed: ADCH.2, ADCH1.2
unnamed: ADCH.3, ADCH1.3
unnamed: ADCH.4, ADCH1.4
unnamed: ADCH.5, ADCH1.5
unnamed: ADCH.6, ADCH1.6
unnamed: ADCH.7, ADCH1.7
unnamed: ADCH.8, ADCH1.8
unnamed: AUX2.1, JP2.15
unnamed: AUX2.2, JP2.13
unnamed: AUX2.3, JP2.11
unnamed: AUX2.4, JP2.9
unnamed: AUX2.5, JP2.7
unnamed: AUX2.6, JP2.5
unnamed: AUX2.7, JP2.3
unnamed: AUX2.8, JP2.1
unnamed: AUX1.1, PWML.1
unnamed: AUX1.2, PWML.2
unnamed: AUX1.3, PWML.3
unnamed: AUX1.4, PWML.4
unnamed: AUX1.5, PWML.5
unnamed: AUX1.6, PWML.6
unnamed: AUX1.7, PWML.7
RESET: POWER.1, S2.2 (S)
VCC: JP3.1, JP4.1, JP8.1, JP8.3, JP8.5, R1.P$1 (1), VCC.1, Z-AXIS.VDD

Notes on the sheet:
Laser Arduino Mega Pololu Shield

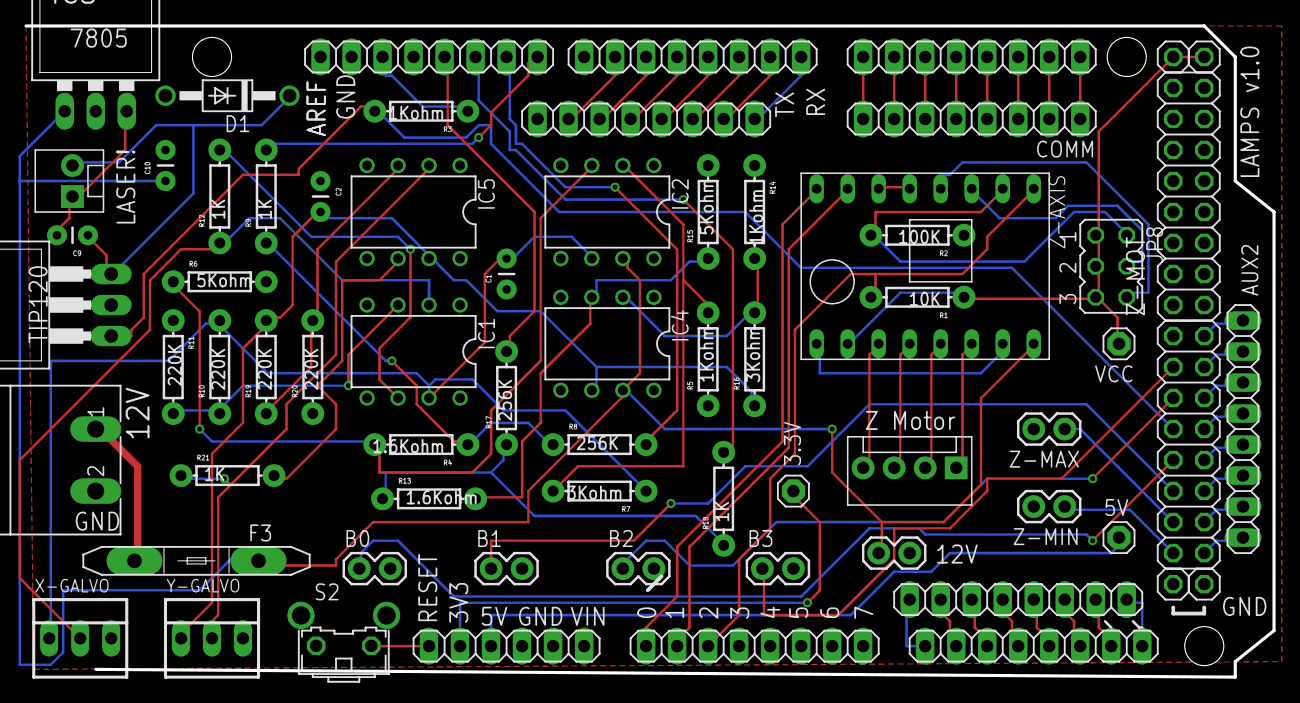
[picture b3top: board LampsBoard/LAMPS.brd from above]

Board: 2 copper layers, 102.2 x 53.3 mm, 67 parts (0 on the bottom side), 78 nets.

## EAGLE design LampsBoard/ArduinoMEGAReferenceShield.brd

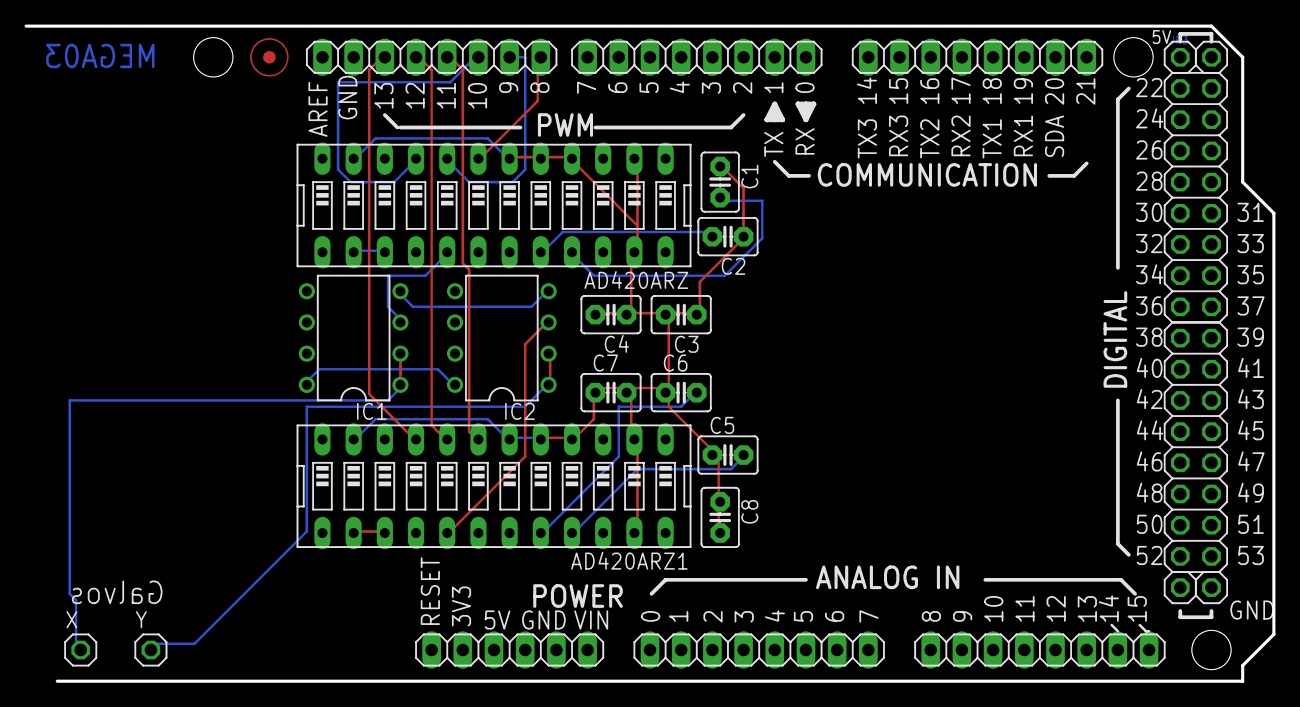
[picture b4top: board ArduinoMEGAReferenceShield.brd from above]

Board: 2 copper layers, 101.6 x 53.3 mm, 27 parts (0 on the bottom side), 19 nets.

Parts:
AD420ARZ, AD420ARZ1: EDG-12
ADCH: 8-15; 1X08
ADCL: 0-7; 1X08
C1, C2, C5, C6: 10 nF; C2.5-3
C3, C4, C7, C8: 100 nF; C2.5-3
COMMUNICATION: 14-21 (TX3 RX3 TX2 RX2 TX1 RX1 SDA); 1X08
IC1, IC2: LM358N; DIL08
JP1: 22-37; 2X08
JP2: 38-53; 2X08
JP3, JP4: +5V; 1X01
JP5, JP6: GND; 1X01
POWER: Reset 3v3 5V GND Vin; 1X06
PWMH: 8-13 GND AREF; 1X08
PWML: RX(0) TX(1) 2-7; 1X08
U$3: FIDUCIALMOUNT; FIDUCIA-MOUNT
X: 1X01
Y: 1X01

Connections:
D8: AD420ARZ.7, PWMH.1
D9: AD420ARZ.8, PWMH.2
D10: AD420ARZ.9, PWMH.3
D11: AD420ARZ1.7, PWMH.4
D12: AD420ARZ1.8, PWMH.5
D13: AD420ARZ1.9, PWMH.6
GND: AD420ARZ.2, AD420ARZ.4, AD420ARZ.5, AD420ARZ.6, AD420ARZ.11, AD420ARZ.23, AD420ARZ1.2, AD420ARZ1.4, AD420ARZ1.5, AD420ARZ1.6, AD420ARZ1.11, AD420ARZ1.23, C1.1, C2.1, C3.1, C3.2, C4.1, C4.2, C5.1, C6.1, C7.1, C7.2, C8.1, C8.2
unnamed: AD420ARZ1.21, C5.2
unnamed: AD420ARZ1.20, C6.2
unnamed: AD420ARZ.21, C1.2
unnamed: AD420ARZ.20, C2.2
unnamed: AD420ARZ.17, IC1.3
unnamed: AD420ARZ.14, AD420ARZ.15
unnamed: IC1.1, IC1.2, X.1
unnamed: AD420ARZ1.17, IC2.3
unnamed: AD420ARZ1.14, AD420ARZ1.15
unnamed: IC2.1, IC2.2, Y.1
V+: IC1.8, IC2.8
V-: IC1.4, IC2.4

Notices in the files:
Lamps2.0/LAMPS.sch:
Copyright 2012 Justin Hawkins
GPL v3
pcb_design/Lamps2.1/LAMPS.brd:
2013 c (GPL)
pcb_design/Lamps2.1/LAMPS.sch:
prYntech 2013 (c) GPL
parts and their libraries:
SparkFun: Licensing: CC v3.0 Share-Alike You are welcome to use this library for commercial purposes.
